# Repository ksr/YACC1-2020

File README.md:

# YACC1-2020 (Yet Another Custom CPU)

Finally time to try building a custom CPU from basic TTL and other "simple" ICs (no 74ls181 ALU, that would be cheating :-) ). 

The YACC1-2020, provides the tools and resources to learn computer science starting from the basics of digital logic through to a fully working custom CPU with a user defined instruction set, assembler, BASIC interpreter, and one day an operating system with filesystem, command line interpreter, and utilities.

The project is currently under development as a personal project. The basic idea has been kicking around inside my head for years (47 years to be exact), but until recently never made it to the top of my list (I did make an attempt a few years back but life got in the way). Now I am exploring if this project might be interesting to others, perhaps as an educational tool or maybe just a fun project.

Here is a [video of the machine in operation](https://youtu.be/6pjIE4_MxIA) and some photos can be found in the Photos & Videos subdirectory in this repository

The basic system is comprised of 7 cards:
- Memory card with 64k RAM and 32K ROM (total address space 64K) The memory card also contains two temporary registers
- Register card, each with 4 16-bit registers that can drive data or address bus, although the system can operate with one register card anything really useful will require two cards. The system has control lines to support upto 4 register cards for a total of 16 registers
- IO Card has serveral options; Serial RS-232, 8-bit switches, 8-bit LED, LCD
- ALU Card supports the boolean, compare, add/sub operations, and the accumulator
- Sequencer 2 card set made up of a memory card and logic card mated together (see photos)
- Optional but highly revommended Bus Test Card, this allows driving the bus in test mode and monitoring the bus in listening mode

## Motivation

Like many others, back in the mid 1970s I had the opportunity to learn both computer programming and microcomputer hardware simultaneously. For me it all started with programming BASIC on a timeshare HP machine via a terminal and/or optical hollerith cards. My math teacher who also taught computer programming allowed us to use the termoianl if we finished our work early. At home I also dabbled with digital circuits and when Popular Electronics published the COSMAC ELF project I was hooked. Now I wonder if for some students when learning computer science does the hardware seem too much like a magic box.

If this project is of intertest, perhaps your one of the following:<br/>
- High school computer science educators<br/>
- Freshman and sophomore college computer science educators<br/>
- Electronics or Retro computer enthusiast<br/>
- Or just generally interested
	
Please reach out to ken at cottageworker dot com

## Directories

### Data Sheets:
		Useful data sheets, manuals, references.
			(These are all readily available online but if I inadvertently violated copyright
			please let me know and I will remove immediately)

### General Notes:
		System wide notes, more specific notes in various subdirectories
		
### PCB:
		PCB designs, there are two different subdirectories:
			Production: These are the latest fully functioning designs, most likely currently in use
			Working - Underdevelopment: These are the newest versions of the boards in design
		Each board has or will have a "theory of operation" document
			
### Photos & Videos:
		Some sharable files

### Presentations:
		Presentations related to the YACC1-2020 project
		
### Software:
		All software related to the project, see subdirectory for more information
		
### Utilities:
		Arduino: Configuration files for Arduino code
		Clocker: External Arduino based to tool for single step debug operations
		Eagle: Configuration files for Eagle
		Waveforms: Timing diagrams for cpu instructions, probably should move to software area

### YACC1 Connector - V3.2.pdf
		Current bus connector specifications
		
<br/><br/> 
-- Thanks for taking a look --

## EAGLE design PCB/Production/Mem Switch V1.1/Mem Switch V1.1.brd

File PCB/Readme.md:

# PCB Files

## Production
This are the latest versions of boards ordered. That does not mean they are fully tested and working. See the notes file in each subdirectory for additional status information.

## Working - Under Development
These boards have not been ordered, they are still in a developement phase. See notes file in each subdirectory for addtional informaition

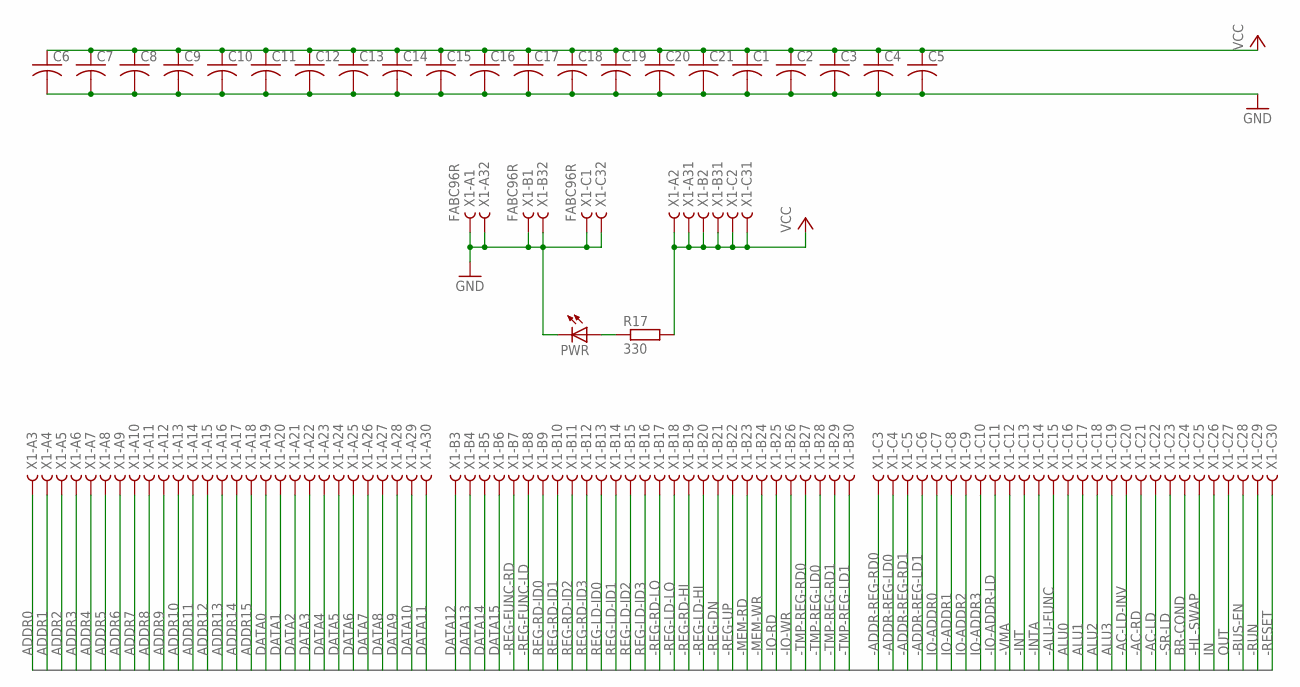
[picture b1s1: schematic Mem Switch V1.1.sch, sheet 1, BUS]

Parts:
C1, C2, C3, C4, C5, C6, C7, C8, C9, C10, C11, C12, C13, C14, C15, C16, C17, C18, C19, C20, C21: C-US025-025X050; C025-025X050
PWR: LED5MM
R17: 330; 0207/10
X1: FABC96R

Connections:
-AC-LD: X1.C22
-AC-LD-INV: X1.C20
-AC-RD: X1.C21
-ADDR-REG-LD0: X1.C4
-ADDR-REG-LD1: X1.C6
-ADDR-REG-RD0: X1.C3
-ADDR-REG-RD1: X1.C5
-ALU-FUNC: X1.C15
-BUS-EN: X1.C28; also elsewhere on the board
-HL-SWAP: X1.C25
-INT: X1.C13
-INTA: X1.C14
-IO-ADDR-LD: X1.C11
-IO-RD: X1.B25
-IO-WR: X1.B26
-MEM-RD: X1.B23; also elsewhere on the board
-MEM-WR: X1.B24
-REG-DN: X1.B21
-REG-FUNC-LD: X1.B8
-REG-FUNC-RD: X1.B7
-REG-LD-HI: X1.B20
-REG-LD-LO: X1.B18
-REG-RD-HI: X1.B19
-REG-RD-LO: X1.B17
-REG-UP: X1.B22
-RESET: X1.C30
-RUN: X1.C29
-SR-LD: X1.C23
-TMP-REG-LD0: X1.B28
-TMP-REG-LD1: X1.B30
-TMP-REG-RD0: X1.B27
-TMP-REG-RD1: X1.B29
-VMA: X1.C12; also elsewhere on the board
ADDR0: X1.A3; also elsewhere on the board
ADDR1: X1.A4; also elsewhere on the board
ADDR2: X1.A5; also elsewhere on the board
ADDR3: X1.A6; also elsewhere on the board
ADDR4: X1.A7; also elsewhere on the board
ADDR5: X1.A8; also elsewhere on the board
ADDR6: X1.A9; also elsewhere on the board
ADDR7: X1.A10; also elsewhere on the board
ADDR8: X1.A11; also elsewhere on the board
ADDR9: X1.A12; also elsewhere on the board
ADDR10: X1.A13; also elsewhere on the board
ADDR11: X1.A14; also elsewhere on the board
ADDR12: X1.A15; also elsewhere on the board
ADDR13: X1.A16; also elsewhere on the board
ADDR14: X1.A17; also elsewhere on the board
ADDR15: X1.A18; also elsewhere on the board
ALU0: X1.C16
ALU1: X1.C17
ALU2: X1.C18
ALU3: X1.C19
BR-COND: X1.C24
DATA0: X1.A19; also elsewhere on the board
DATA1: X1.A20; also elsewhere on the board
DATA2: X1.A21; also elsewhere on the board
DATA3: X1.A22; also elsewhere on the board
DATA4: X1.A23; also elsewhere on the board
DATA5: X1.A24; also elsewhere on the board
DATA6: X1.A25; also elsewhere on the board
DATA7: X1.A26; also elsewhere on the board
DATA8: X1.A27
DATA9: X1.A28
DATA10: X1.A29
DATA11: X1.A30
DATA12: X1.B3
DATA13: X1.B4
DATA14: X1.B5
DATA15: X1.B6
GND: C1.2, C2.2, C3.2, C4.2, C5.2, C6.2, C7.2, C8.2, C9.2, C10.2, C11.2, C12.2, C13.2, C14.2, C15.2, C16.2, C17.2, C18.2, C19.2, C20.2, C21.2, PWR.K (C), X1.A1, X1.A32, X1.B1, X1.B32, X1.C1, X1.C32; also elsewhere on the board
IN: X1.C26
IO-ADDR0: X1.C7
IO-ADDR1: X1.C8
IO-ADDR2: X1.C9
IO-ADDR3: X1.C10
unnamed: PWR.A, R17.1
OUT: X1.C27
REG-LD-ID0: X1.B13
REG-LD-ID1: X1.B14
REG-LD-ID2: X1.B15
REG-LD-ID3: X1.B16
REG-RD-ID0: X1.B9
REG-RD-ID1: X1.B10
REG-RD-ID2: X1.B11
REG-RD-ID3: X1.B12
VCC: C1.1, C2.1, C3.1, C4.1, C5.1, C6.1, C7.1, C8.1, C9.1, C10.1, C11.1, C12.1, C13.1, C14.1, C15.1, C16.1, C17.1, C18.1, C19.1, C20.1, C21.1, R17.2, X1.A2, X1.A31, X1.B2, X1.B31, X1.C2, X1.C31; also elsewhere on the board

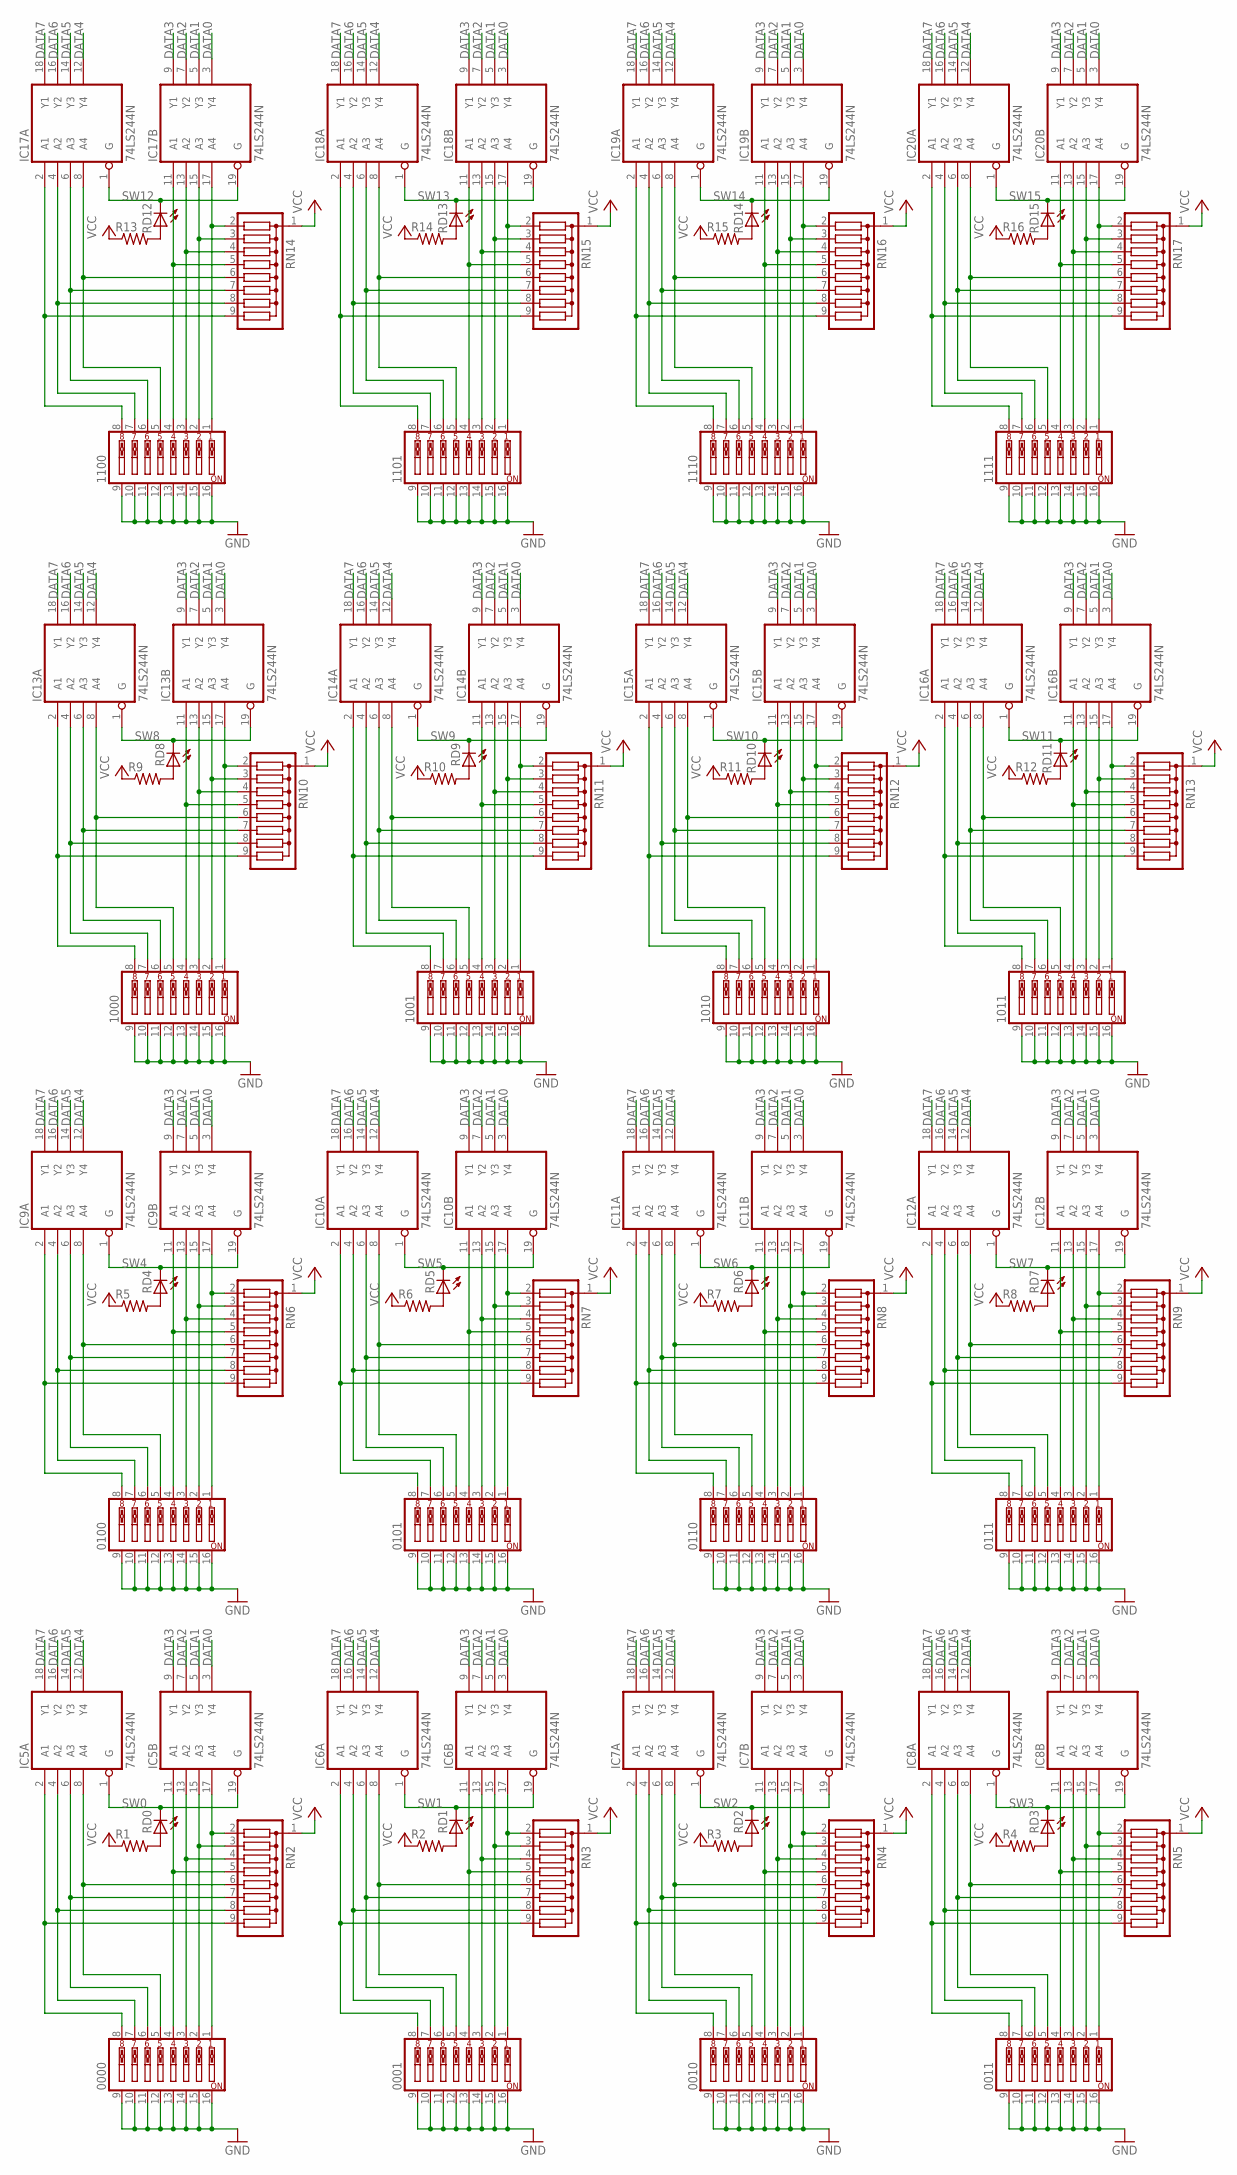
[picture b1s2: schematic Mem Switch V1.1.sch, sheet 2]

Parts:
0000, 0001, 0010, 0011, 0100, 0101, 0110, 0111, 1000, 1001, 1010, 1011, 1100, 1101, 1110, 1111: SW_DIP-8; EDG-08
IC5, IC6, IC7, IC8, IC9, IC10, IC11, IC12, IC13, IC14, IC15, IC16, IC17, IC18, IC19, IC20: 74LS244N; DIL20
R1, R2, R3, R4, R5, R6, R7, R8, R9, R10, R11, R12, R13, R14, R15, R16: R-US_0207/10; 0207/10
RD0, RD1, RD2, RD3, RD4, RD5, RD6, RD7, RD8, RD9, RD10, RD11, RD12, RD13, RD14, RD15: LED3MM
RN2, RN3, RN4, RN5, RN6, RN7, RN8, RN9, RN10, RN11, RN12, RN13, RN14, RN15, RN16, RN17: G08R; SIL9

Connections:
DATA0: IC5.3 (Y4), IC6.3 (Y4), IC7.3 (Y4), IC8.3 (Y4), IC9.3 (Y4), IC10.3 (Y4), IC11.3 (Y4), IC12.3 (Y4), IC13.3 (Y4), IC14.3 (Y4), IC15.3 (Y4), IC16.3 (Y4), IC17.3 (Y4), IC18.3 (Y4), IC19.3 (Y4), IC20.3 (Y4); also elsewhere on the board
DATA1: IC5.5 (Y3), IC6.5 (Y3), IC7.5 (Y3), IC8.5 (Y3), IC9.5 (Y3), IC10.5 (Y3), IC11.5 (Y3), IC12.5 (Y3), IC13.5 (Y3), IC14.5 (Y3), IC15.5 (Y3), IC16.5 (Y3), IC17.5 (Y3), IC18.5 (Y3), IC19.5 (Y3), IC20.5 (Y3); also elsewhere on the board
DATA2: IC5.7 (Y2), IC6.7 (Y2), IC7.7 (Y2), IC8.7 (Y2), IC9.7 (Y2), IC10.7 (Y2), IC11.7 (Y2), IC12.7 (Y2), IC13.7 (Y2), IC14.7 (Y2), IC15.7 (Y2), IC16.7 (Y2), IC17.7 (Y2), IC18.7 (Y2), IC19.7 (Y2), IC20.7 (Y2); also elsewhere on the board
DATA3: IC5.9 (Y1), IC6.9 (Y1), IC7.9 (Y1), IC8.9 (Y1), IC9.9 (Y1), IC10.9 (Y1), IC11.9 (Y1), IC12.9 (Y1), IC13.9 (Y1), IC14.9 (Y1), IC15.9 (Y1), IC16.9 (Y1), IC17.9 (Y1), IC18.9 (Y1), IC19.9 (Y1), IC20.9 (Y1); also elsewhere on the board
DATA4: IC5.12 (Y4), IC6.12 (Y4), IC7.12 (Y4), IC8.12 (Y4), IC9.12 (Y4), IC10.12 (Y4), IC11.12 (Y4), IC12.12 (Y4), IC13.12 (Y4), IC14.12 (Y4), IC15.12 (Y4), IC16.12 (Y4), IC17.12 (Y4), IC18.12 (Y4), IC19.12 (Y4), IC20.12 (Y4); also elsewhere on the board
DATA5: IC5.14 (Y3), IC6.14 (Y3), IC7.14 (Y3), IC8.14 (Y3), IC9.14 (Y3), IC10.14 (Y3), IC11.14 (Y3), IC12.14 (Y3), IC13.14 (Y3), IC14.14 (Y3), IC15.14 (Y3), IC16.14 (Y3), IC17.14 (Y3), IC18.14 (Y3), IC19.14 (Y3), IC20.14 (Y3); also elsewhere on the board
DATA6: IC5.16 (Y2), IC6.16 (Y2), IC7.16 (Y2), IC8.16 (Y2), IC9.16 (Y2), IC10.16 (Y2), IC11.16 (Y2), IC12.16 (Y2), IC13.16 (Y2), IC14.16 (Y2), IC15.16 (Y2), IC16.16 (Y2), IC17.16 (Y2), IC18.16 (Y2), IC19.16 (Y2), IC20.16 (Y2); also elsewhere on the board
DATA7: IC5.18 (Y1), IC6.18 (Y1), IC7.18 (Y1), IC8.18 (Y1), IC9.18 (Y1), IC10.18 (Y1), IC11.18 (Y1), IC12.18 (Y1), IC13.18 (Y1), IC14.18 (Y1), IC15.18 (Y1), IC16.18 (Y1), IC17.18 (Y1), IC18.18 (Y1), IC19.18 (Y1), IC20.18 (Y1); also elsewhere on the board
GND: 0000.9, 0000.10, 0000.11, 0000.12, 0000.13, 0000.14, 0000.15, 0000.16, 0001.9, 0001.10, 0001.11, 0001.12, 0001.13, 0001.14, 0001.15, 0001.16, 0010.9, 0010.10, 0010.11, 0010.12, 0010.13, 0010.14, 0010.15, 0010.16, 0011.9, 0011.10, 0011.11, 0011.12, 0011.13, 0011.14, 0011.15, 0011.16, 0100.9, 0100.10, 0100.11, 0100.12, 0100.13, 0100.14, 0100.15, 0100.16, 0101.9, 0101.10, 0101.11, 0101.12, 0101.13, 0101.14, 0101.15, 0101.16, 0110.9, 0110.10, 0110.11, 0110.12, 0110.13, 0110.14, 0110.15, 0110.16, 0111.9, 0111.10, 0111.11, 0111.12, 0111.13, 0111.14, 0111.15, 0111.16, 1000.9, 1000.10, 1000.11, 1000.12, 1000.13, 1000.14, 1000.15, 1000.16, 1001.9, 1001.10, 1001.11, 1001.12, 1001.13, 1001.14, 1001.15, 1001.16, 1010.9, 1010.10, 1010.11, 1010.12, 1010.13, 1010.14, 1010.15, 1010.16, 1011.9, 1011.10, 1011.11, 1011.12, 1011.13, 1011.14, 1011.15, 1011.16, 1100.9, 1100.10, 1100.11, 1100.12, 1100.13, 1100.14, 1100.15, 1100.16, 1101.9, 1101.10, 1101.11, 1101.12, 1101.13, 1101.14, 1101.15, 1101.16, 1110.9, 1110.10, 1110.11, 1110.12, 1110.13, 1110.14, 1110.15, 1110.16, 1111.9, 1111.10, 1111.11, 1111.12, 1111.13, 1111.14, 1111.15, 1111.16, IC5.10 (GND), IC6.10 (GND), IC7.10 (GND), IC8.10 (GND), IC9.10 (GND), IC10.10 (GND), IC11.10 (GND), IC12.10 (GND), IC13.10 (GND), IC14.10 (GND), IC15.10 (GND), IC16.10 (GND), IC17.10 (GND), IC18.10 (GND), IC19.10 (GND), IC20.10 (GND); also elsewhere on the board
unnamed: 0000.1, IC5.17 (A4), RN2.2
unnamed: 0000.2, IC5.15 (A3), RN2.3
unnamed: 0000.3, IC5.13 (A2), RN2.4
unnamed: 0000.4, IC5.11 (A1), RN2.5
unnamed: 0000.5, IC5.8 (A4), RN2.6
unnamed: 0000.6, IC5.6 (A3), RN2.7
unnamed: 0000.7, IC5.4 (A2), RN2.8
unnamed: 0000.8, IC5.2 (A1), RN2.9
unnamed: 0001.1, IC6.17 (A4), RN3.2
unnamed: 0001.2, IC6.15 (A3), RN3.3
unnamed: 0001.3, IC6.13 (A2), RN3.4
unnamed: 0001.4, IC6.11 (A1), RN3.5
unnamed: 0001.5, IC6.8 (A4), RN3.6
unnamed: 0001.6, IC6.6 (A3), RN3.7
unnamed: 0001.7, IC6.4 (A2), RN3.8
unnamed: 0001.8, IC6.2 (A1), RN3.9
unnamed: 0010.1, IC7.17 (A4), RN4.2
unnamed: 0010.2, IC7.15 (A3), RN4.3
unnamed: 0010.3, IC7.13 (A2), RN4.4
unnamed: 0010.4, IC7.11 (A1), RN4.5
unnamed: 0010.5, IC7.8 (A4), RN4.6
unnamed: 0010.6, IC7.6 (A3), RN4.7
unnamed: 0010.7, IC7.4 (A2), RN4.8
unnamed: 0010.8, IC7.2 (A1), RN4.9
unnamed: 0011.1, IC8.17 (A4), RN5.2
unnamed: 0011.2, IC8.15 (A3), RN5.3
unnamed: 0011.3, IC8.13 (A2), RN5.4
unnamed: 0011.4, IC8.11 (A1), RN5.5
unnamed: 0011.5, IC8.8 (A4), RN5.6
unnamed: 0011.6, IC8.6 (A3), RN5.7
unnamed: 0011.7, IC8.4 (A2), RN5.8
unnamed: 0011.8, IC8.2 (A1), RN5.9
unnamed: 0100.1, IC9.17 (A4), RN6.2
unnamed: 0100.2, IC9.15 (A3), RN6.3
unnamed: 0100.3, IC9.13 (A2), RN6.4
unnamed: 0100.4, IC9.11 (A1), RN6.5
unnamed: 0100.5, IC9.8 (A4), RN6.6
unnamed: 0100.6, IC9.6 (A3), RN6.7
unnamed: 0100.7, IC9.4 (A2), RN6.8
unnamed: 0100.8, IC9.2 (A1), RN6.9
unnamed: 0101.1, IC10.17 (A4), RN7.2
unnamed: 0101.2, IC10.15 (A3), RN7.3
unnamed: 0101.3, IC10.13 (A2), RN7.4
unnamed: 0101.4, IC10.11 (A1), RN7.5
unnamed: 0101.5, IC10.8 (A4), RN7.6
unnamed: 0101.6, IC10.6 (A3), RN7.7
unnamed: 0101.7, IC10.4 (A2), RN7.8
unnamed: 0101.8, IC10.2 (A1), RN7.9
unnamed: 0110.1, IC11.17 (A4), RN8.2
unnamed: 0110.2, IC11.15 (A3), RN8.3
unnamed: 0110.3, IC11.13 (A2), RN8.4
unnamed: 0110.4, IC11.11 (A1), RN8.5
unnamed: 0110.5, IC11.8 (A4), RN8.6
unnamed: 0110.6, IC11.6 (A3), RN8.7
unnamed: 0110.7, IC11.4 (A2), RN8.8
unnamed: 0110.8, IC11.2 (A1), RN8.9
unnamed: 0111.1, IC12.17 (A4), RN9.2
unnamed: 0111.2, IC12.15 (A3), RN9.3
unnamed: 0111.3, IC12.13 (A2), RN9.4
unnamed: 0111.4, IC12.11 (A1), RN9.5
unnamed: 0111.5, IC12.8 (A4), RN9.6
unnamed: 0111.6, IC12.6 (A3), RN9.7
unnamed: 0111.7, IC12.4 (A2), RN9.8
unnamed: 0111.8, IC12.2 (A1), RN9.9
unnamed: 1000.1, IC13.17 (A4), RN10.2
unnamed: 1000.2, IC13.15 (A3), RN10.3
unnamed: 1000.3, IC13.13 (A2), RN10.4
unnamed: 1000.4, IC13.11 (A1), RN10.5
unnamed: 1000.5, IC13.8 (A4), RN10.6
unnamed: 1000.6, IC13.6 (A3), RN10.7
unnamed: 1000.7, IC13.4 (A2), RN10.8
unnamed: 1000.8, IC13.2 (A1), RN10.9
unnamed: 1001.1, IC14.17 (A4), RN11.2
unnamed: 1001.2, IC14.15 (A3), RN11.3
unnamed: 1001.3, IC14.13 (A2), RN11.4
unnamed: 1001.4, IC14.11 (A1), RN11.5
unnamed: 1001.5, IC14.8 (A4), RN11.6
unnamed: 1001.6, IC14.6 (A3), RN11.7
unnamed: 1001.7, IC14.4 (A2), RN11.8
unnamed: 1001.8, IC14.2 (A1), RN11.9
unnamed: R1.2, RD0.A
unnamed: 1010.1, IC15.17 (A4), RN12.2
unnamed: 1010.2, IC15.15 (A3), RN12.3
unnamed: 1010.3, IC15.13 (A2), RN12.4
unnamed: 1010.4, IC15.11 (A1), RN12.5
unnamed: 1010.5, IC15.8 (A4), RN12.6
unnamed: 1010.6, IC15.6 (A3), RN12.7
unnamed: 1010.7, IC15.4 (A2), RN12.8
unnamed: 1010.8, IC15.2 (A1), RN12.9
unnamed: R2.2, RD1.A
unnamed: 1011.1, IC16.17 (A4), RN13.2
unnamed: 1011.2, IC16.15 (A3), RN13.3
unnamed: 1011.3, IC16.13 (A2), RN13.4
unnamed: 1011.4, IC16.11 (A1), RN13.5
unnamed: 1011.5, IC16.8 (A4), RN13.6
unnamed: 1011.6, IC16.6 (A3), RN13.7
unnamed: 1011.7, IC16.4 (A2), RN13.8
unnamed: 1011.8, IC16.2 (A1), RN13.9
unnamed: R3.2, RD2.A
unnamed: 1100.1, IC17.17 (A4), RN14.2
unnamed: 1100.2, IC17.15 (A3), RN14.3
unnamed: 1100.3, IC17.13 (A2), RN14.4
unnamed: 1100.4, IC17.11 (A1), RN14.5
unnamed: 1100.5, IC17.8 (A4), RN14.6
unnamed: 1100.6, IC17.6 (A3), RN14.7
unnamed: 1100.7, IC17.4 (A2), RN14.8
unnamed: 1100.8, IC17.2 (A1), RN14.9
unnamed: R4.2, RD3.A
unnamed: 1101.1, IC18.17 (A4), RN15.2
unnamed: 1101.2, IC18.15 (A3), RN15.3
unnamed: 1101.3, IC18.13 (A2), RN15.4
unnamed: 1101.4, IC18.11 (A1), RN15.5
unnamed: 1101.5, IC18.8 (A4), RN15.6
unnamed: 1101.6, IC18.6 (A3), RN15.7
unnamed: 1101.7, IC18.4 (A2), RN15.8
unnamed: 1101.8, IC18.2 (A1), RN15.9
unnamed: R5.2, RD4.A
unnamed: 1110.1, IC19.17 (A4), RN16.2
unnamed: 1110.2, IC19.15 (A3), RN16.3
unnamed: 1110.3, IC19.13 (A2), RN16.4
unnamed: 1110.4, IC19.11 (A1), RN16.5
unnamed: 1110.5, IC19.8 (A4), RN16.6
unnamed: 1110.6, IC19.6 (A3), RN16.7
unnamed: 1110.7, IC19.4 (A2), RN16.8
unnamed: 1110.8, IC19.2 (A1), RN16.9
unnamed: R6.2, RD5.A
unnamed: 1111.1, IC20.17 (A4), RN17.2
unnamed: 1111.2, IC20.15 (A3), RN17.3
unnamed: 1111.3, IC20.13 (A2), RN17.4
unnamed: 1111.4, IC20.11 (A1), RN17.5
unnamed: 1111.5, IC20.8 (A4), RN17.6
unnamed: 1111.6, IC20.6 (A3), RN17.7
unnamed: 1111.7, IC20.4 (A2), RN17.8
unnamed: 1111.8, IC20.2 (A1), RN17.9
unnamed: R7.2, RD6.A
unnamed: R8.2, RD7.A
unnamed: R9.2, RD8.A
unnamed: R10.2, RD9.A
unnamed: R11.2, RD10.A
unnamed: R12.2, RD11.A
unnamed: R13.2, RD12.A
unnamed: R14.2, RD13.A
unnamed: R15.2, RD14.A
unnamed: R16.2, RD15.A
SW0: IC5.1 (G), IC5.19 (G), RD0.K (C); also elsewhere on the board
SW1: IC6.1 (G), IC6.19 (G), RD1.K (C); also elsewhere on the board
SW2: IC7.1 (G), IC7.19 (G), RD2.K (C); also elsewhere on the board
SW3: IC8.1 (G), IC8.19 (G), RD3.K (C); also elsewhere on the board
SW4: IC9.1 (G), IC9.19 (G), RD4.K (C); also elsewhere on the board
SW5: IC10.1 (G), IC10.19 (G), RD5.K (C); also elsewhere on the board
SW6: IC11.1 (G), IC11.19 (G), RD6.K (C); also elsewhere on the board
SW7: IC12.1 (G), IC12.19 (G), RD7.K (C); also elsewhere on the board
SW8: IC13.1 (G), IC13.19 (G), RD8.K (C); also elsewhere on the board
SW9: IC14.1 (G), IC14.19 (G), RD9.K (C); also elsewhere on the board
SW10: IC15.1 (G), IC15.19 (G), RD10.K (C); also elsewhere on the board
SW11: IC16.1 (G), IC16.19 (G), RD11.K (C); also elsewhere on the board
SW12: IC17.1 (G), IC17.19 (G), RD12.K (C); also elsewhere on the board
SW13: IC18.1 (G), IC18.19 (G), RD13.K (C); also elsewhere on the board
SW14: IC19.1 (G), IC19.19 (G), RD14.K (C); also elsewhere on the board
SW15: IC20.1 (G), IC20.19 (G), RD15.K (C); also elsewhere on the board
VCC: IC5.20 (VCC), IC6.20 (VCC), IC7.20 (VCC), IC8.20 (VCC), IC9.20 (VCC), IC10.20 (VCC), IC11.20 (VCC), IC12.20 (VCC), IC13.20 (VCC), IC14.20 (VCC), IC15.20 (VCC), IC16.20 (VCC), IC17.20 (VCC), IC18.20 (VCC), IC19.20 (VCC), IC20.20 (VCC), R1.1, R2.1, R3.1, R4.1, R5.1, R6.1, R7.1, R8.1, R9.1, R10.1, R11.1, R12.1, R13.1, R14.1, R15.1, R16.1, RN2.1, RN3.1, RN4.1, RN5.1, RN6.1, RN7.1, RN8.1, RN9.1, RN10.1, RN11.1, RN12.1, RN13.1, RN14.1, RN15.1, RN16.1, RN17.1; also elsewhere on the board

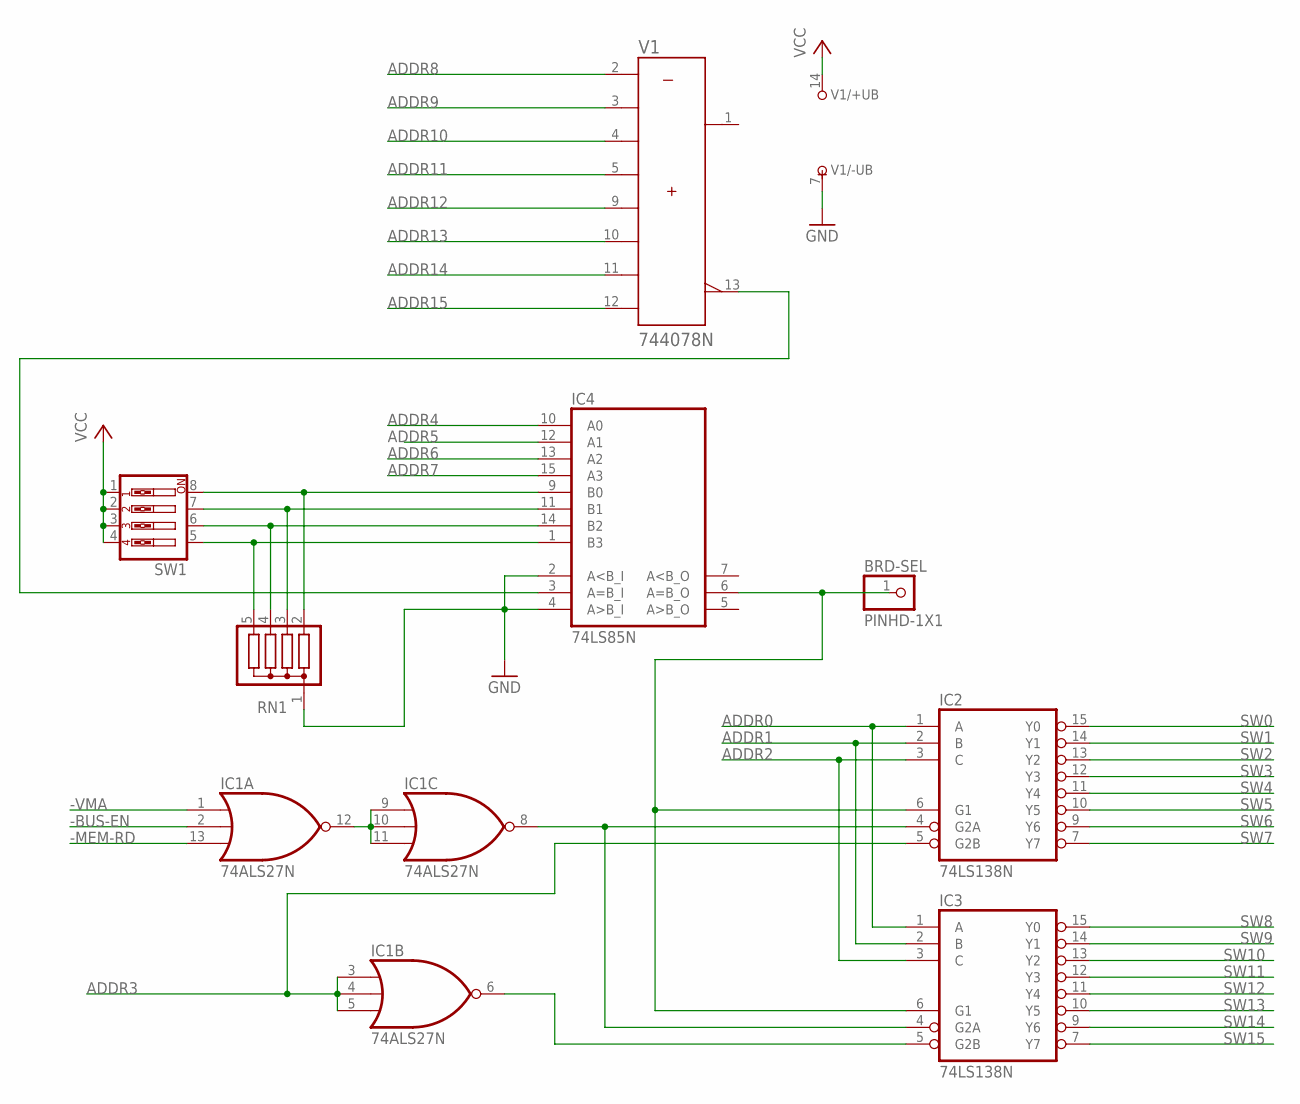
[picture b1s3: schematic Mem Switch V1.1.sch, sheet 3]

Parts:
BRD-SEL: PINHD-1X1; 1X01
IC1: 74ALS27N; DIL14
IC2, IC3: 74LS138N; DIL16
IC4: 74LS85N; DIL16
RN1: G04R; SIL5
SW1: SW_DIP-4; EDG-04
V1: 744078N; DIL14

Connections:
-BUS-EN: IC1.2 (I1); also elsewhere on the board
-MEM-RD: IC1.13 (I2); also elsewhere on the board
-VMA: IC1.1 (I0); also elsewhere on the board
ADDR0: IC2.1 (A), IC3.1 (A); also elsewhere on the board
ADDR1: IC2.2 (B), IC3.2 (B); also elsewhere on the board
ADDR2: IC2.3 (C), IC3.3 (C); also elsewhere on the board
ADDR3: IC1.3 (I0), IC1.4 (I1), IC1.5 (I2), IC2.5 (G2B); also elsewhere on the board
ADDR4: IC4.10 (A0); also elsewhere on the board
ADDR5: IC4.12 (A1); also elsewhere on the board
ADDR6: IC4.13 (A2); also elsewhere on the board
ADDR7: IC4.15 (A3); also elsewhere on the board
ADDR8: V1.2 (A); also elsewhere on the board
ADDR9: V1.3 (B); also elsewhere on the board
ADDR10: V1.4 (C); also elsewhere on the board
ADDR11: V1.5 (D); also elsewhere on the board
ADDR12: V1.9 (E); also elsewhere on the board
ADDR13: V1.10 (F); also elsewhere on the board
ADDR14: V1.11 (G); also elsewhere on the board
ADDR15: V1.12 (H); also elsewhere on the board
GND: IC1.7 (GND), IC2.8 (GND), IC3.8 (GND), IC4.2 (A<B_I), IC4.4 (A>B_I), IC4.8 (GND), RN1.1, V1.7 (-UB); also elsewhere on the board
unnamed: BRD-SEL.1, IC2.6 (G1), IC3.6 (G1), IC4.6 (A=B_O)
unnamed: IC1.9 (I0), IC1.10 (I1), IC1.11 (I2), IC1.12 (O)
unnamed: IC4.9 (B0), RN1.2, SW1.8
unnamed: IC1.6 (O), IC3.5 (G2B)
unnamed: IC4.11 (B1), RN1.3, SW1.7
unnamed: IC4.3 (A=B_I), V1.13 (W)
unnamed: IC4.14 (B2), RN1.4, SW1.6
unnamed: IC4.1 (B3), RN1.5, SW1.5
unnamed: IC1.8 (O), IC2.4 (G2A), IC3.4 (G2A)
SW0: IC2.15 (Y0); also elsewhere on the board
SW1: IC2.14 (Y1); also elsewhere on the board
SW2: IC2.13 (Y2); also elsewhere on the board
SW3: IC2.12 (Y3); also elsewhere on the board
SW4: IC2.11 (Y4); also elsewhere on the board
SW5: IC2.10 (Y5); also elsewhere on the board
SW6: IC2.9 (Y6); also elsewhere on the board
SW7: IC2.7 (Y7); also elsewhere on the board
SW8: IC3.15 (Y0); also elsewhere on the board
SW9: IC3.14 (Y1); also elsewhere on the board
SW10: IC3.13 (Y2); also elsewhere on the board
SW11: IC3.12 (Y3); also elsewhere on the board
SW12: IC3.11 (Y4); also elsewhere on the board
SW13: IC3.10 (Y5); also elsewhere on the board
SW14: IC3.9 (Y6); also elsewhere on the board
SW15: IC3.7 (Y7); also elsewhere on the board
VCC: IC1.14 (VCC), IC2.16 (VCC), IC3.16 (VCC), IC4.16 (VCC), SW1.1, SW1.2, SW1.3, SW1.4, V1.14 (+UB); also elsewhere on the board

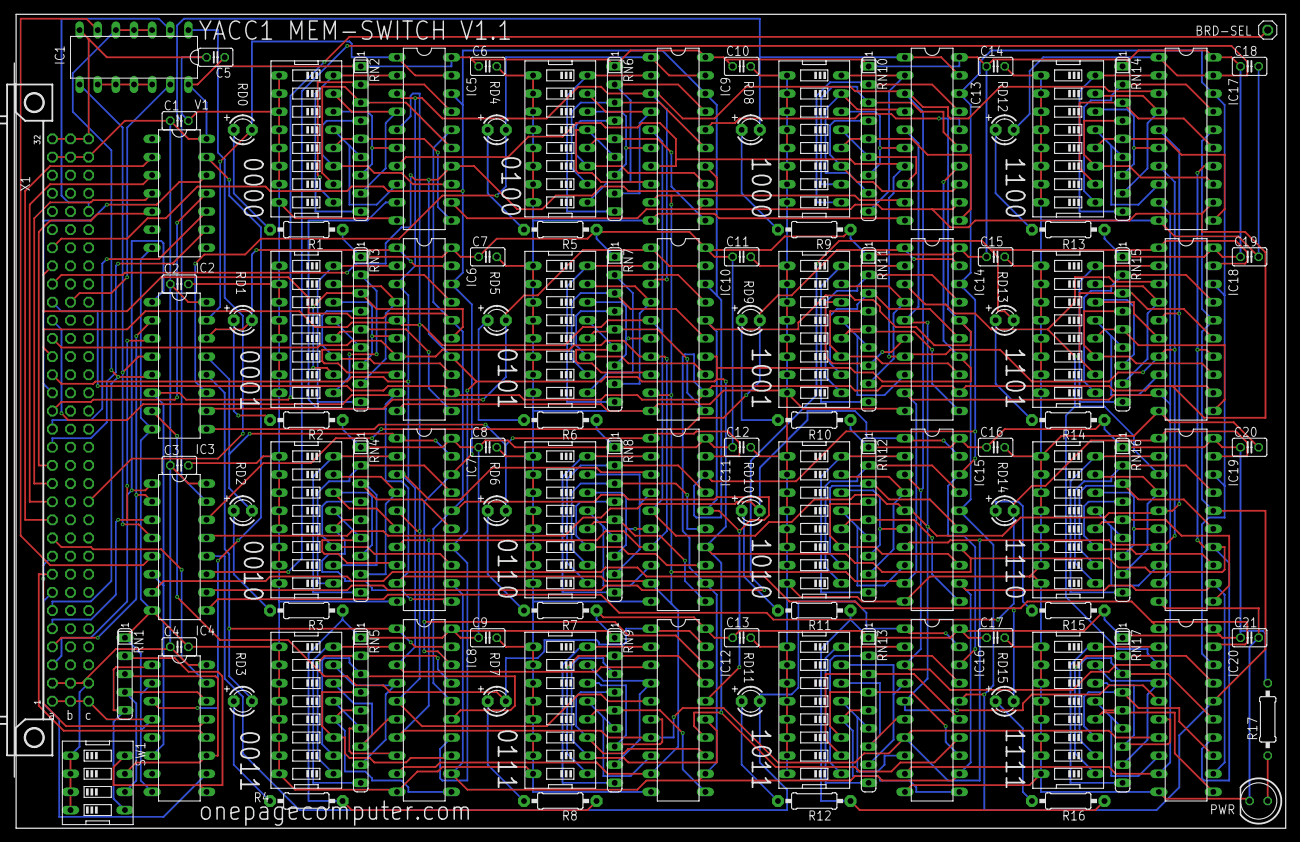
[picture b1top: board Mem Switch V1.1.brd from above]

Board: 2 copper layers, 177.8 x 114.0 mm, 112 parts (0 on the bottom side), 199 nets.

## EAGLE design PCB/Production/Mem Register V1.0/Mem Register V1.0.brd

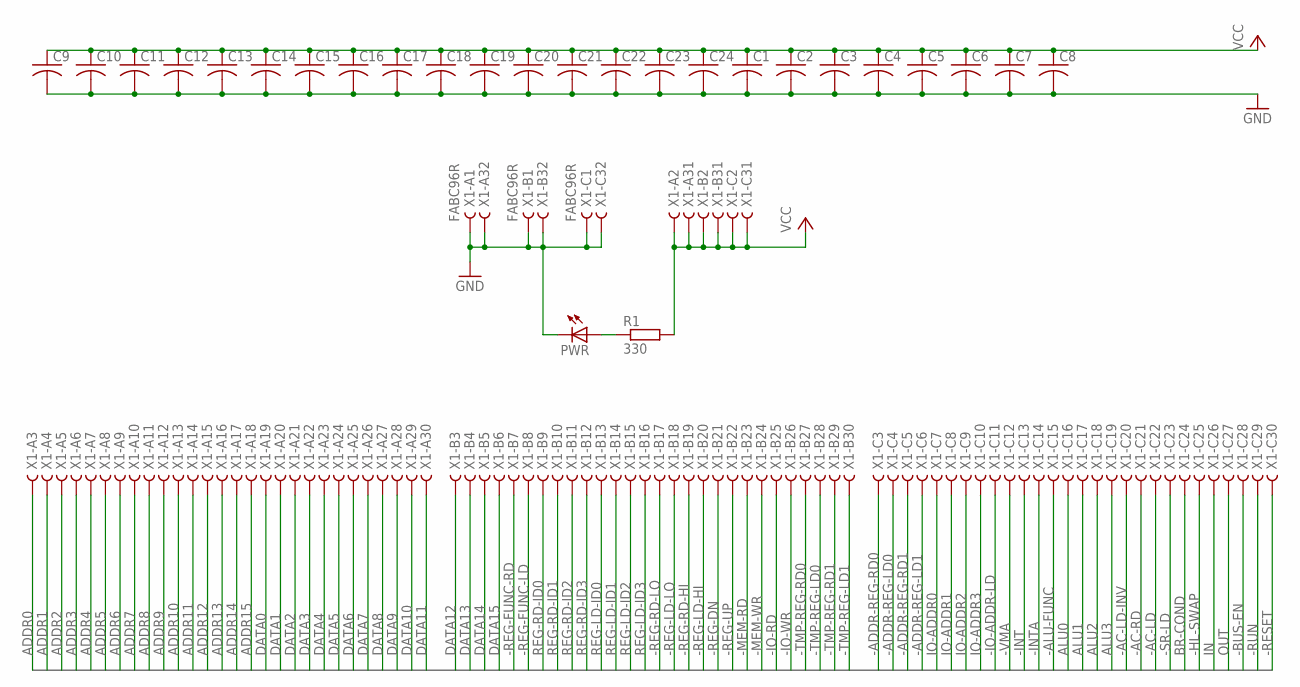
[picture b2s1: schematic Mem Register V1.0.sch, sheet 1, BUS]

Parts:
C1, C2, C3, C4, C5, C6, C7, C8, C9, C10, C11, C12, C13, C14, C15, C16, C17, C18, C19, C20, C21, C22, C23, C24: C-US025-025X050; C025-025X050
PWR: LED5MM
R1: 330; 0207/10
X1: FABC96R

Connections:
-AC-LD: X1.C22
-AC-LD-INV: X1.C20
-AC-RD: X1.C21
-ADDR-REG-LD0: X1.C4
-ADDR-REG-LD1: X1.C6
-ADDR-REG-RD0: X1.C3
-ADDR-REG-RD1: X1.C5
-ALU-FUNC: X1.C15
-BUS-EN: X1.C28; also elsewhere on the board
-HL-SWAP: X1.C25
-INT: X1.C13
-INTA: X1.C14
-IO-ADDR-LD: X1.C11
-IO-RD: X1.B25
-IO-WR: X1.B26
-MEM-RD: X1.B23; also elsewhere on the board
-MEM-WR: X1.B24; also elsewhere on the board
-REG-DN: X1.B21
-REG-FUNC-LD: X1.B8
-REG-FUNC-RD: X1.B7
-REG-LD-HI: X1.B20
-REG-LD-LO: X1.B18
-REG-RD-HI: X1.B19
-REG-RD-LO: X1.B17
-REG-UP: X1.B22
-RESET: X1.C30
-RUN: X1.C29
-SR-LD: X1.C23
-TMP-REG-LD0: X1.B28
-TMP-REG-LD1: X1.B30
-TMP-REG-RD0: X1.B27
-TMP-REG-RD1: X1.B29
-VMA: X1.C12; also elsewhere on the board
ADDR0: X1.A3; also elsewhere on the board
ADDR1: X1.A4; also elsewhere on the board
ADDR2: X1.A5; also elsewhere on the board
ADDR3: X1.A6; also elsewhere on the board
ADDR4: X1.A7; also elsewhere on the board
ADDR5: X1.A8; also elsewhere on the board
ADDR6: X1.A9; also elsewhere on the board
ADDR7: X1.A10; also elsewhere on the board
ADDR8: X1.A11; also elsewhere on the board
ADDR9: X1.A12; also elsewhere on the board
ADDR10: X1.A13; also elsewhere on the board
ADDR11: X1.A14; also elsewhere on the board
ADDR12: X1.A15; also elsewhere on the board
ADDR13: X1.A16; also elsewhere on the board
ADDR14: X1.A17; also elsewhere on the board
ADDR15: X1.A18; also elsewhere on the board
ALU0: X1.C16
ALU1: X1.C17
ALU2: X1.C18
ALU3: X1.C19
BR-COND: X1.C24
DATA0: X1.A19; also elsewhere on the board
DATA1: X1.A20; also elsewhere on the board
DATA2: X1.A21; also elsewhere on the board
DATA3: X1.A22; also elsewhere on the board
DATA4: X1.A23; also elsewhere on the board
DATA5: X1.A24; also elsewhere on the board
DATA6: X1.A25; also elsewhere on the board
DATA7: X1.A26; also elsewhere on the board
DATA8: X1.A27
DATA9: X1.A28
DATA10: X1.A29
DATA11: X1.A30
DATA12: X1.B3
DATA13: X1.B4
DATA14: X1.B5
DATA15: X1.B6
GND: C1.2, C2.2, C3.2, C4.2, C5.2, C6.2, C7.2, C8.2, C9.2, C10.2, C11.2, C12.2, C13.2, C14.2, C15.2, C16.2, C17.2, C18.2, C19.2, C20.2, C21.2, C22.2, C23.2, C24.2, PWR.K (C), X1.A1, X1.A32, X1.B1, X1.B32, X1.C1, X1.C32; also elsewhere on the board
IN: X1.C26
IO-ADDR0: X1.C7
IO-ADDR1: X1.C8
IO-ADDR2: X1.C9
IO-ADDR3: X1.C10
unnamed: PWR.A, R1.1
OUT: X1.C27
REG-LD-ID0: X1.B13
REG-LD-ID1: X1.B14
REG-LD-ID2: X1.B15
REG-LD-ID3: X1.B16
REG-RD-ID0: X1.B9
REG-RD-ID1: X1.B10
REG-RD-ID2: X1.B11
REG-RD-ID3: X1.B12
VCC: C1.1, C2.1, C3.1, C4.1, C5.1, C6.1, C7.1, C8.1, C9.1, C10.1, C11.1, C12.1, C13.1, C14.1, C15.1, C16.1, C17.1, C18.1, C19.1, C20.1, C21.1, C22.1, C23.1, C24.1, R1.2, X1.A2, X1.A31, X1.B2, X1.B31, X1.C2, X1.C31; also elsewhere on the board

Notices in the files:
parts and their libraries:
SparkFun-Connectors: Licensing: Creative Commons ShareAlike 4.0 International - https://creativecommons.org/licenses/by-sa/4.0
SparkFun-Electromechanical: Licensing: CC v3.0 Share-Alike You are welcome to use this library for commercial purposes.
